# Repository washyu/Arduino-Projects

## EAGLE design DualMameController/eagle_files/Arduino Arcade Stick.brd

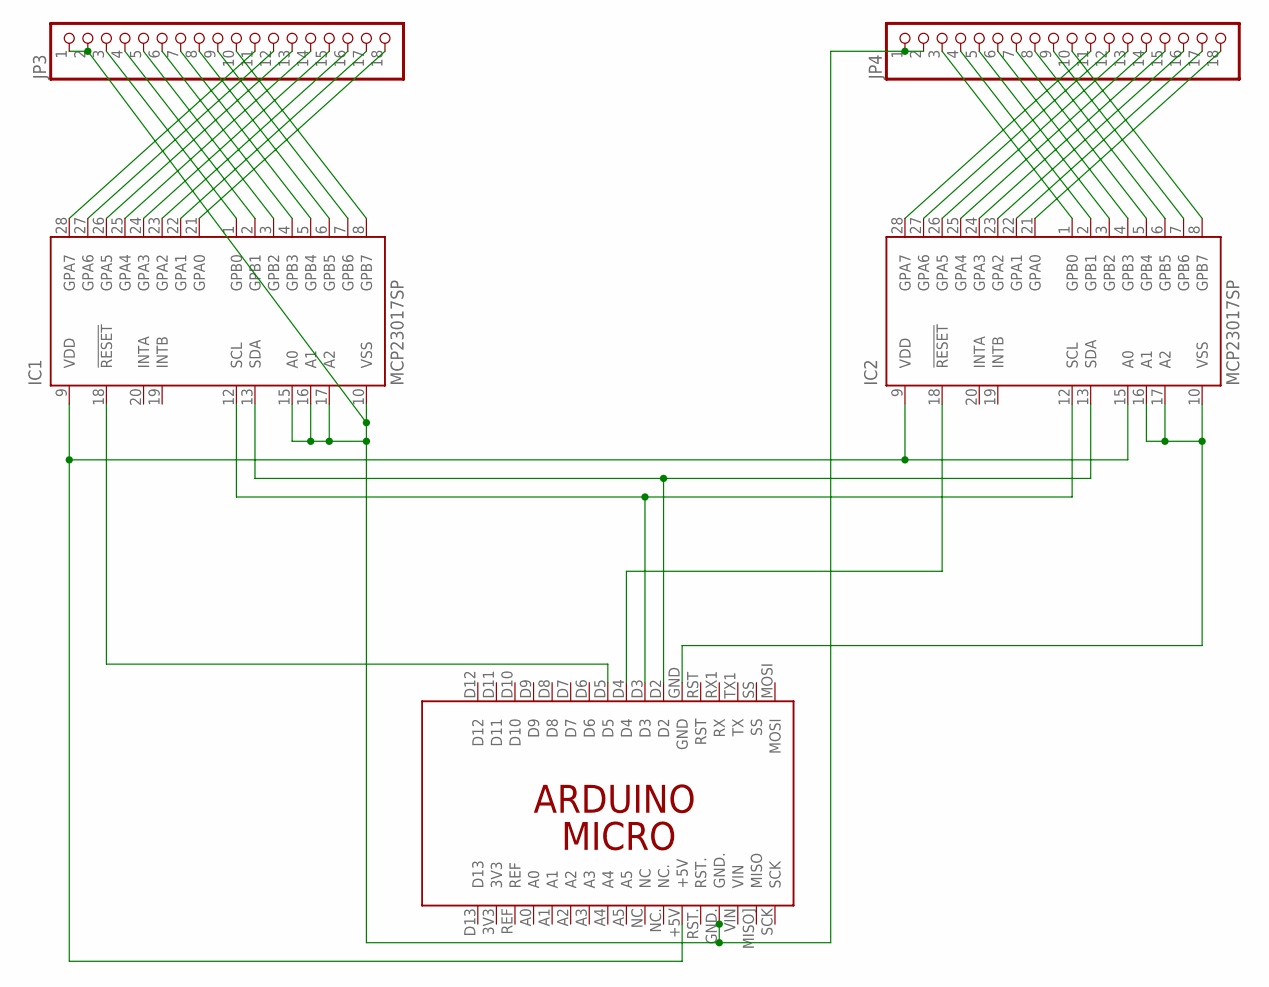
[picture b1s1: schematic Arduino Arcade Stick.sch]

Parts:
IC1, IC2: MCP23017SP; DIL28-3
JP3, JP4: PINHD-1X18; 1X18
PCB1: ARDUINO_MICRO

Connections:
unnamed: IC1.21 (GPA0), JP3.18
unnamed: IC1.22 (GPA1), JP3.17
unnamed: IC1.23 (GPA2), JP3.16
unnamed: IC1.24 (GPA3), JP3.15
unnamed: IC1.25 (GPA4), JP3.14
unnamed: IC1.26 (GPA5), JP3.13
unnamed: IC1.27 (GPA6), JP3.12
unnamed: IC1.28 (GPA7), JP3.11
unnamed: IC1.8 (GPB7), JP3.10
unnamed: IC1.7 (GPB6), JP3.9
unnamed: IC1.6 (GPB5), JP3.8
unnamed: IC1.5 (GPB4), JP3.7
unnamed: IC1.4 (GPB3), JP3.6
unnamed: IC1.3 (GPB2), JP3.5
unnamed: IC1.2 (GPB1), JP3.4
unnamed: IC1.1 (GPB0), JP3.3
unnamed: IC2.21 (GPA0), JP4.18
unnamed: IC2.22 (GPA1), JP4.17
unnamed: IC2.23 (GPA2), JP4.16
unnamed: IC2.24 (GPA3), JP4.15
unnamed: IC2.25 (GPA4), JP4.14
unnamed: IC2.26 (GPA5), JP4.13
unnamed: IC2.27 (GPA6), JP4.12
unnamed: IC2.28 (GPA7), JP4.11
unnamed: IC2.8 (GPB7), JP4.10
unnamed: IC2.7 (GPB6), JP4.9
unnamed: IC2.6 (GPB5), JP4.8
unnamed: IC2.5 (GPB4), JP4.7
unnamed: IC2.4 (GPB3), JP4.6
unnamed: IC2.3 (GPB2), JP4.5
unnamed: IC2.2 (GPB1), JP4.4
unnamed: IC2.1 (GPB0), JP4.3
unnamed: IC2.18 (!RESET), PCB1.D4
unnamed: IC1.13 (SDA), IC2.13 (SDA), PCB1.D2
unnamed: IC1.12 (SCL), IC2.12 (SCL), PCB1.D3
unnamed: IC1.18 (!RESET), PCB1.D5
VDD: IC1.9 (VDD), IC2.9 (VDD), IC2.15 (A0), PCB1.+5V
VSS: IC1.10 (VSS), IC1.15 (A0), IC1.16 (A1), IC1.17 (A2), IC2.10 (VSS), IC2.16 (A1), IC2.17 (A2), JP3.1, JP3.2, JP4.1, JP4.2, PCB1.GND, PCB1.GND.

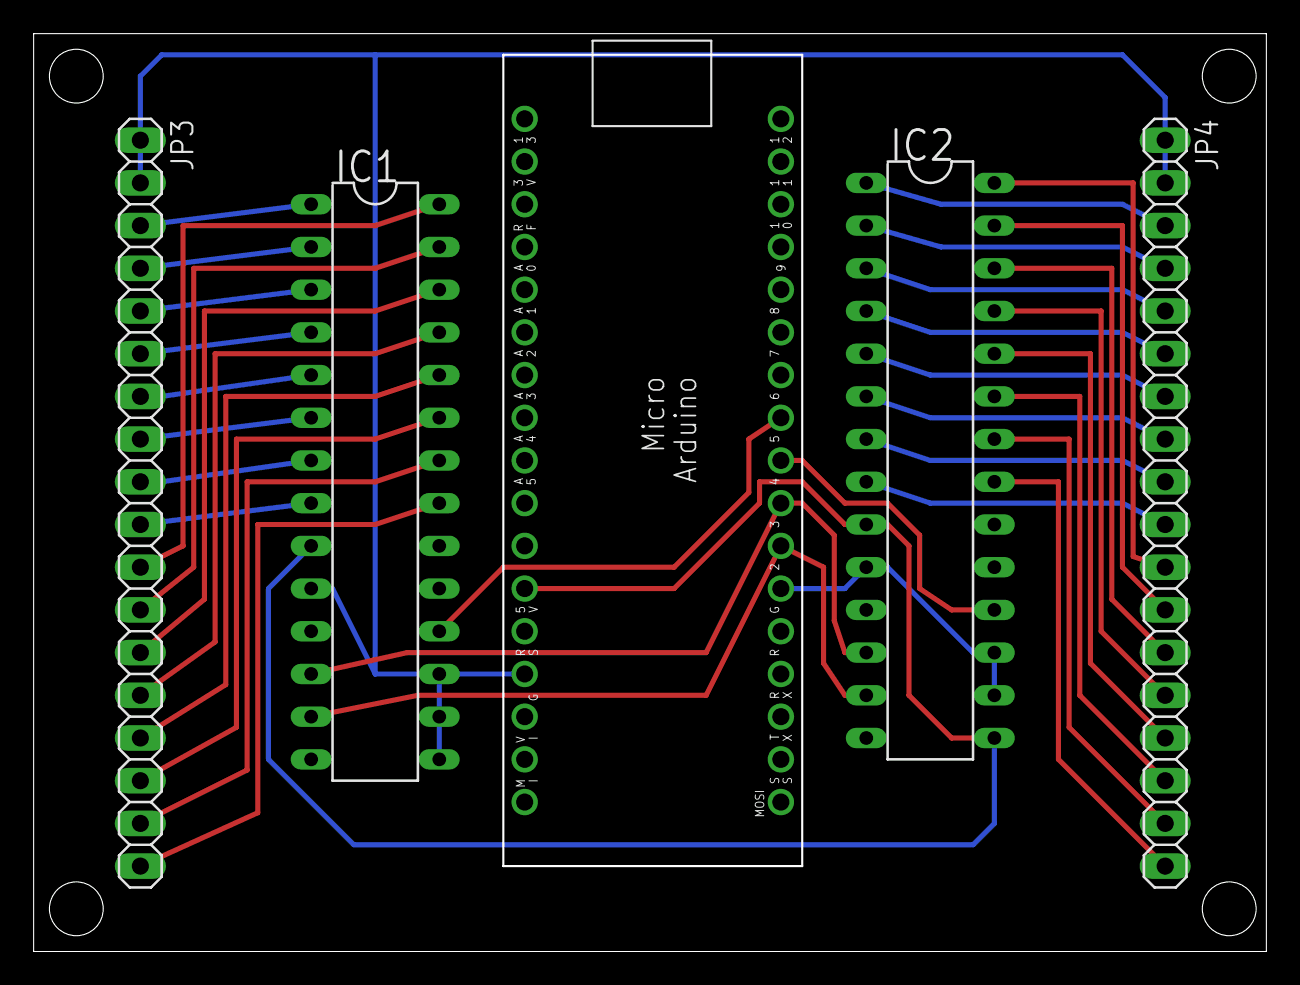
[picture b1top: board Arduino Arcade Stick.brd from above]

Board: 2 copper layers, 73.2 x 54.5 mm, 5 parts (0 on the bottom side), 38 nets.

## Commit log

2014-11-28 First Check-in
2014-12-27 Add Eagle Files
2015-01-18 added some comments and image of the board schematic.
